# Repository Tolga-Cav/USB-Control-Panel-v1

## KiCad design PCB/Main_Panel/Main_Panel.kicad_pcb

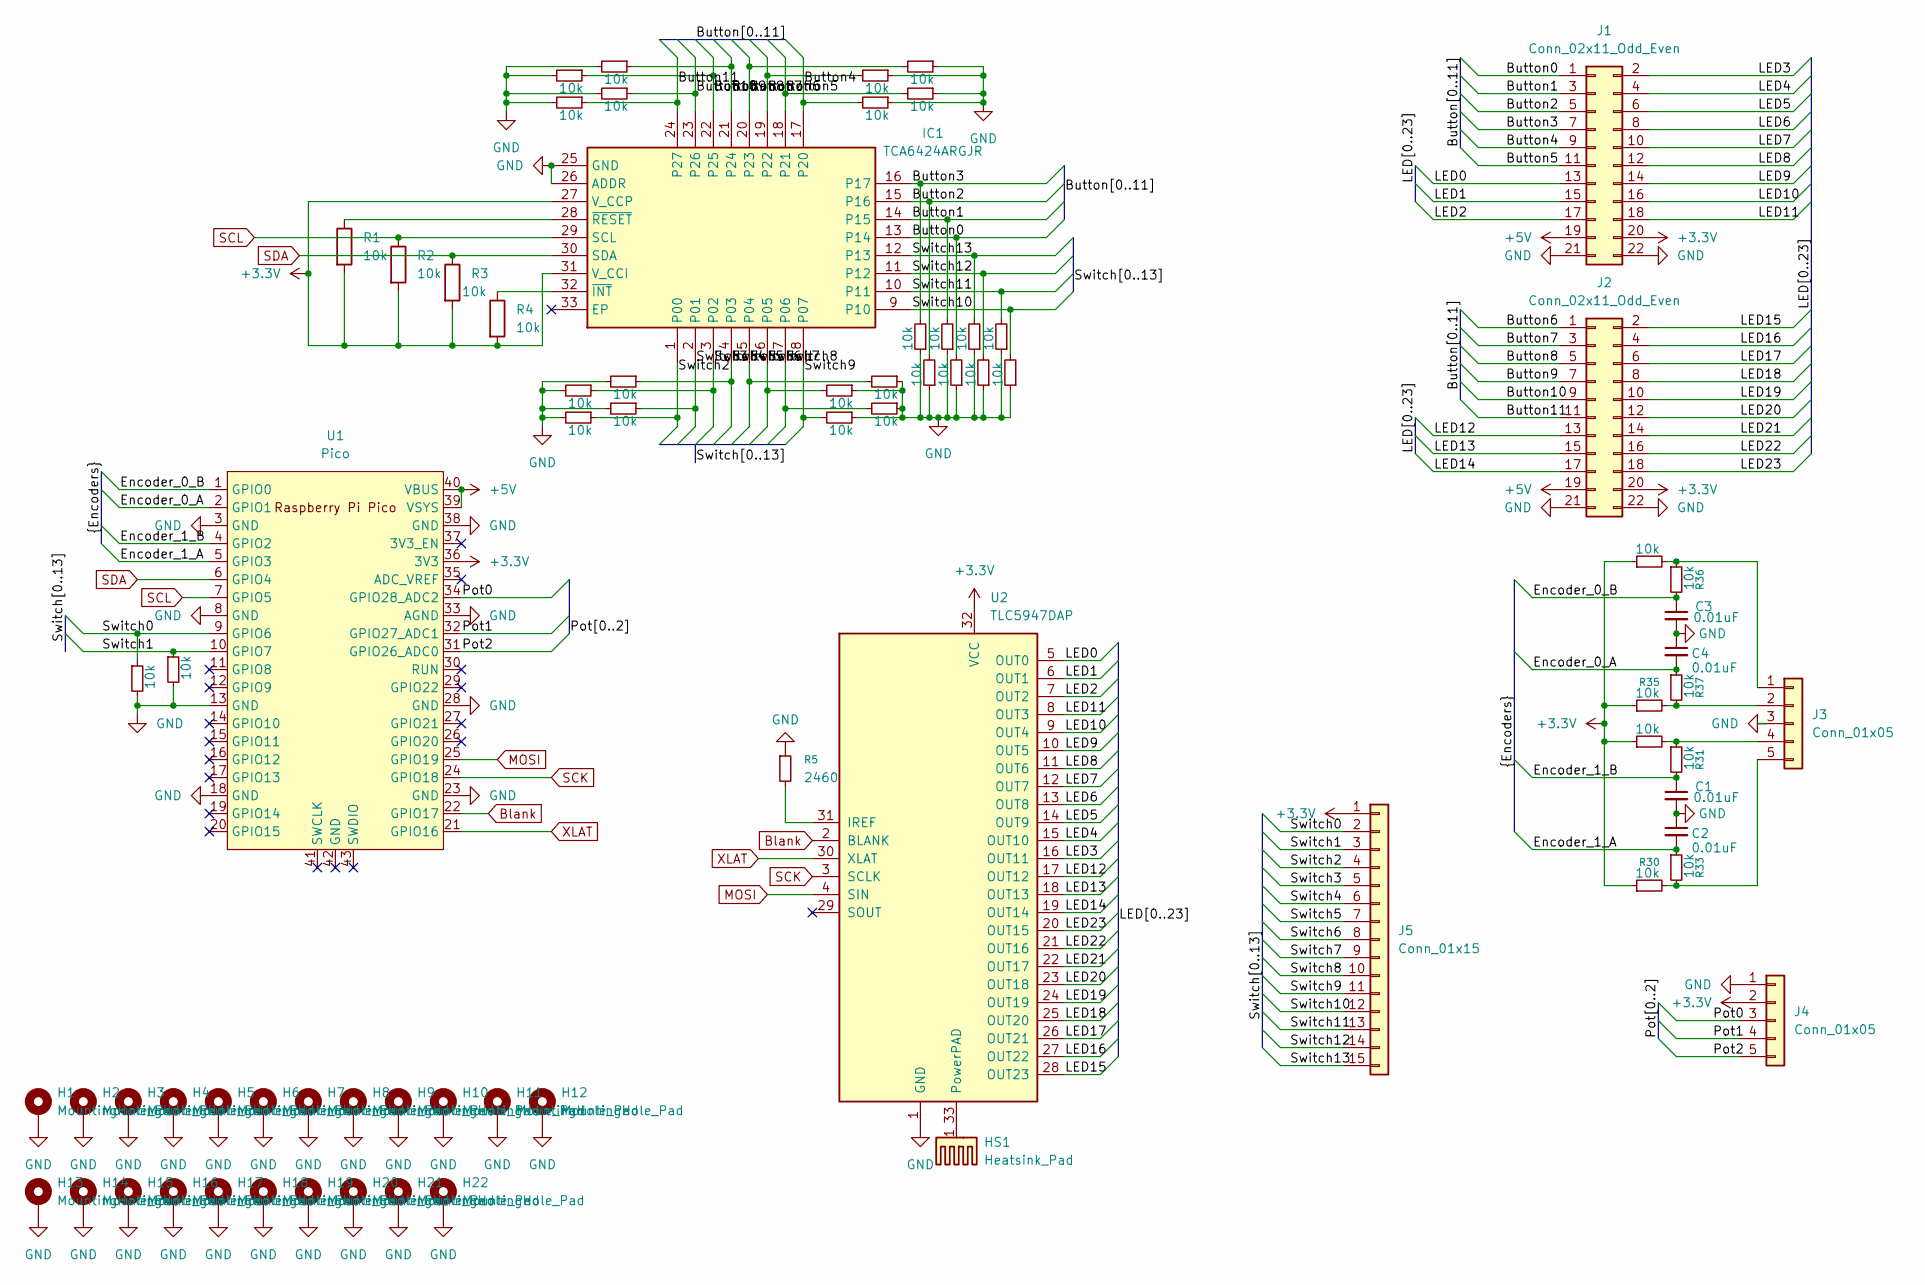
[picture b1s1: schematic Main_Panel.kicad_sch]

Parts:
C1, C2, C3, C4: 0.01uF; C_0805_2012Metric
H1, H2, H3, H4, H5, H6, H7, H8, H9, H10, H11, H12, H13, H14, H15, H16, H17, H18, H19, H20, H21, H22: MountingHole_Pad; MountingHole_3.2mm_M3_DIN965_Pad
HS1: Heatsink_Pad; Heat Sink
IC1: TCA6424ARGJR; QFN50P500X500X60-33N-D; Mouser Part Number 595-TCA6424ARGJR
J1, J2: Conn_02x11_Odd_Even; PinHeader_2x11_P2.54mm_Vertical
J3, J4: Conn_01x05; PinHeader_1x05_P2.54mm_Vertical
J5: Conn_01x15; PinHeader_1x15_P2.54mm_Vertical
R1, R2, R3, R4, R6, R7, R8, R9, R10, R11, R12, R13, R14, R15, R16, R17, R18, R19, R20, R21, R22, R23, R24, R25, R26, R27, R28, R29, R30, R31, R32, R33, R34, R35, R36, R37, R38, R39: 10k; R_0805_2012Metric
R5: 2460; R_0805_2012Metric
U1: Pico; RPi_Pico_SMD_TH
U2: TLC5947DAP; HTSSOP-32-1EP_6.1x11mm_P0.65mm_EP5.2x11mm_Mask4.11x4.36mm_T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

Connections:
+3.3V: IC1.27 (V_CCP), IC1.31 (V_CCI), J1.20, J2.20, J4.2, J5.1, R1.2, R2.2, R3.2, R4.2, R30.1, R32.1, R34.1, R35.1, U1.36 (3V3), U2.32 (VCC)
+5V: J1.19, J2.19, U1.39 (VSYS), U1.40 (VBUS)
/Button0: IC1.13 (P14), J1.1, R10.2
/Button1: IC1.14 (P15), J1.3, R7.2
/Button2: IC1.15 (P16), J1.5, R9.2
/Button3: IC1.16 (P17), J1.7, R6.2
/Button4: IC1.17 (P20), J1.9, R19.2
/Button5: IC1.18 (P21), J1.11, R21.2
/Button6: IC1.19 (P22), J2.1, R18.2
/Button7: IC1.20 (P23), J2.3, R20.2
/Button8: IC1.21 (P24), J2.5, R15.1
/Button9: IC1.22 (P25), J2.7, R14.1
/Button10: IC1.23 (P26), J2.9, R16.1
/Button11: IC1.24 (P27), J2.11, R17.1
/Encoder_0_A: C4.2, R37.1, U1.2 (GPIO1)
/Encoder_0_B: C3.1, R36.2, U1.1 (GPIO0)
/Encoder_1_A: C2.2, R33.1, U1.5 (GPIO3)
/Encoder_1_B: C1.1, R31.2, U1.4 (GPIO2)
/LED0: J1.13, U2.5 (OUT0)
/LED1: J1.15, U2.6 (OUT1)
/LED2: J1.17, U2.7 (OUT2)
/LED3: J1.2, U2.16 (OUT11)
/LED4: J1.4, U2.15 (OUT10)
/LED5: J1.6, U2.14 (OUT9)
/LED6: J1.8, U2.13 (OUT8)
/LED7: J1.10, U2.12 (OUT7)
/LED8: J1.12, U2.11 (OUT6)
/LED9: J1.14, U2.10 (OUT5)
/LED10: J1.16, U2.9 (OUT4)
/LED11: J1.18, U2.8 (OUT3)
/LED12: J2.13, U2.17 (OUT12)
/LED13: J2.15, U2.18 (OUT13)
/LED14: J2.17, U2.19 (OUT14)
/LED15: J2.2, U2.28 (OUT23)
/LED16: J2.4, U2.27 (OUT22)
/LED17: J2.6, U2.26 (OUT21)
/LED18: J2.8, U2.25 (OUT20)
/LED19: J2.10, U2.24 (OUT19)
/LED20: J2.12, U2.23 (OUT18)
/LED21: J2.14, U2.22 (OUT17)
/LED22: J2.16, U2.21 (OUT16)
/LED23: J2.18, U2.20 (OUT15)
/Pot0: J4.3, U1.34 (GPIO28_ADC2)
/Pot1: J4.4, U1.32 (GPIO27_ADC1)
/Pot2: J4.5, U1.31 (GPIO26_ADC0)
/Switch0: J5.2, R38.1, U1.9 (GPIO6)
/Switch1: J5.3, R39.1, U1.10 (GPIO7)
/Switch2: IC1.1 (P00), J5.4, R23.1
/Switch3: IC1.2 (P01), J5.5, R25.1
/Switch4: IC1.3 (P02), J5.6, R22.1
/Switch5: IC1.4 (P03), J5.7, R24.1
/Switch6: IC1.5 (P04), J5.8, R28.2
/Switch7: IC1.6 (P05), J5.9, R26.2
/Switch8: IC1.7 (P06), J5.10, R29.2
/Switch9: IC1.8 (P07), J5.11, R27.2
/Switch10: IC1.9 (P10), J5.12, R13.2
/Switch11: IC1.10 (P11), J5.13, R12.2
/Switch12: IC1.11 (P12), J5.14, R11.2
/Switch13: IC1.12 (P13), J5.15, R8.2
Blank: U1.22 (GPIO17), U2.2 (BLANK)
GND: C1.2, C2.1, C3.2, C4.1, H1.1, H2.1, H3.1, H4.1, H5.1, H6.1, H7.1, H8.1, H9.1, H10.1, H11.1, H12.1, H13.1, H14.1, H15.1, H16.1, H17.1, H18.1, H19.1, H20.1, H21.1, H22.1, IC1.25 (GND), IC1.26 (ADDR), J1.21, J1.22, J2.21, J2.22, J3.3, J4.1, R5.1, R6.1, R7.1, R8.1, R9.1, R10.1, R11.1, R12.1, R13.1, R14.2, R15.2, R16.2, R17.2, R18.1, R19.1, R20.1, R21.1, R22.2, R23.2, R24.2, R25.2, R26.1, R27.1, R28.1, R29.1, R38.2, R39.2, U1.3 (GND), U1.8 (GND), U1.13 (GND), U1.18 (GND), U1.23 (GND), U1.28 (GND), U1.33 (AGND), U1.38 (GND), U2.1 (GND)
MOSI: U1.25 (GPIO19), U2.4 (SIN)
unnamed: IC1.32 (~INT), R4.1
unnamed: IC1.28 (~RESET), R1.1
unnamed: J3.1, R34.2, R36.1
unnamed: J3.2, R35.2, R37.2
unnamed: J3.4, R31.1, R32.2
unnamed: J3.5, R30.2, R33.2
unnamed: R5.2, U2.31 (IREF)
unnamed: HS1.1, U2.33 (PowerPAD)
SCK: U1.24 (GPIO18), U2.3 (SCLK)
SCL: IC1.29 (SCL), R2.1, U1.7 (GPIO5)
SDA: IC1.30 (SDA), R3.1, U1.6 (GPIO4)
XLAT: U1.21 (GPIO16), U2.30 (XLAT)

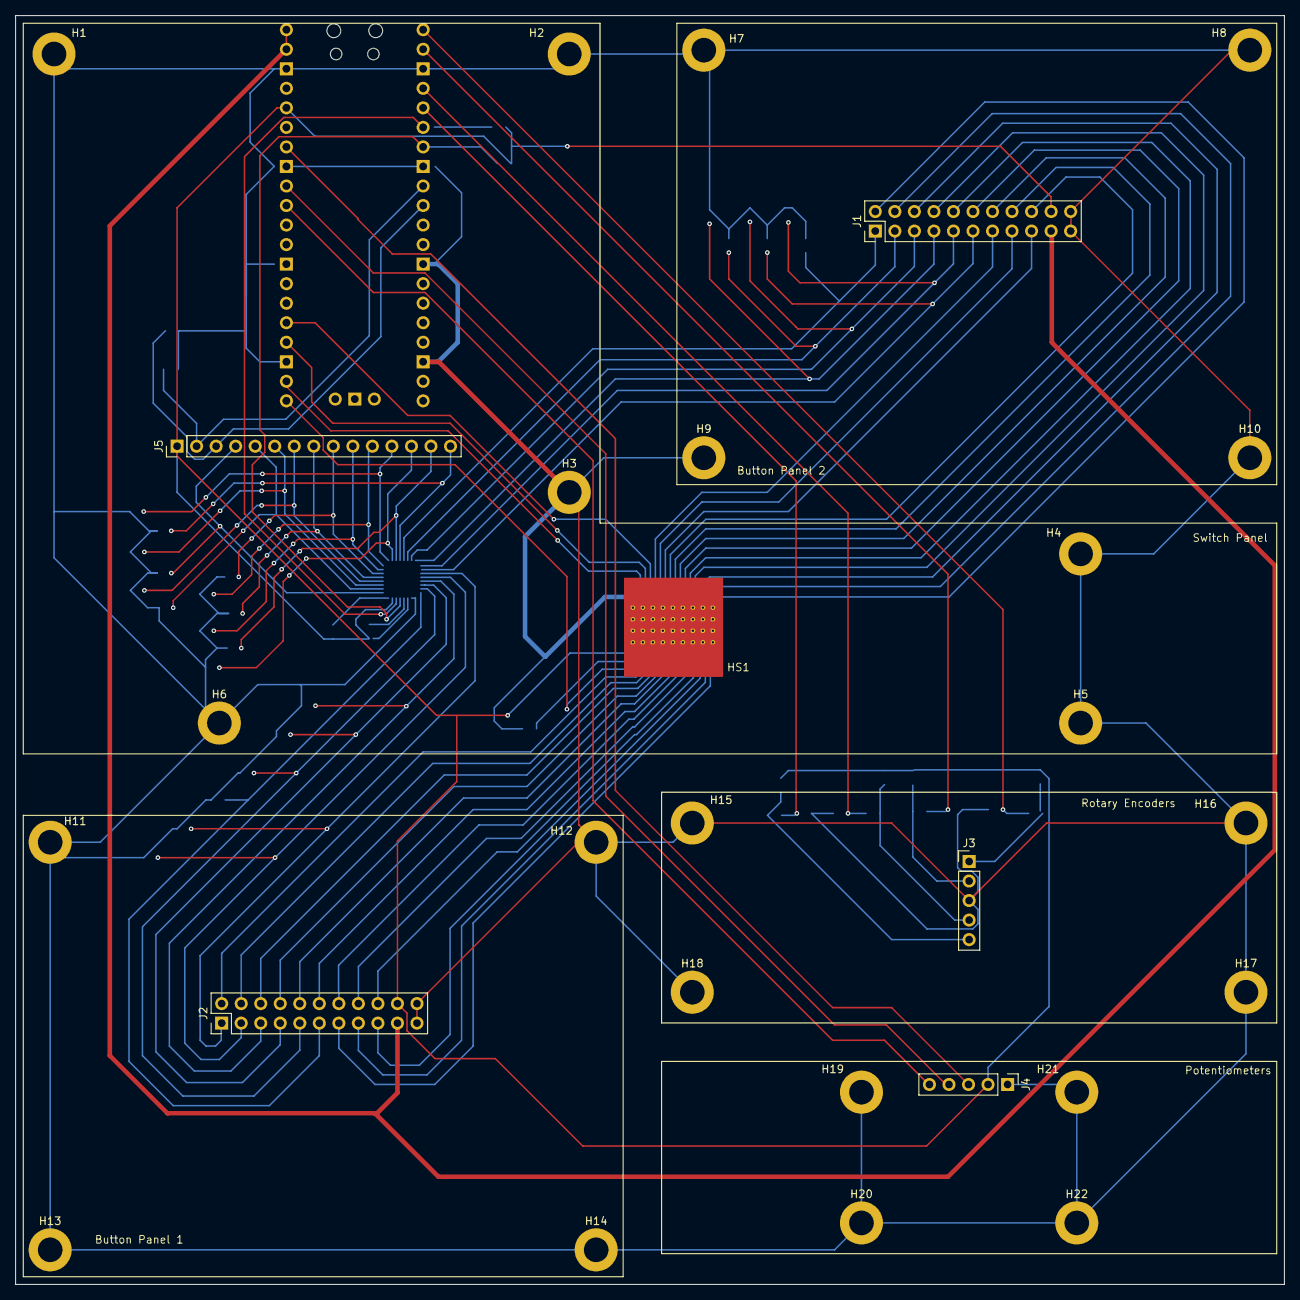
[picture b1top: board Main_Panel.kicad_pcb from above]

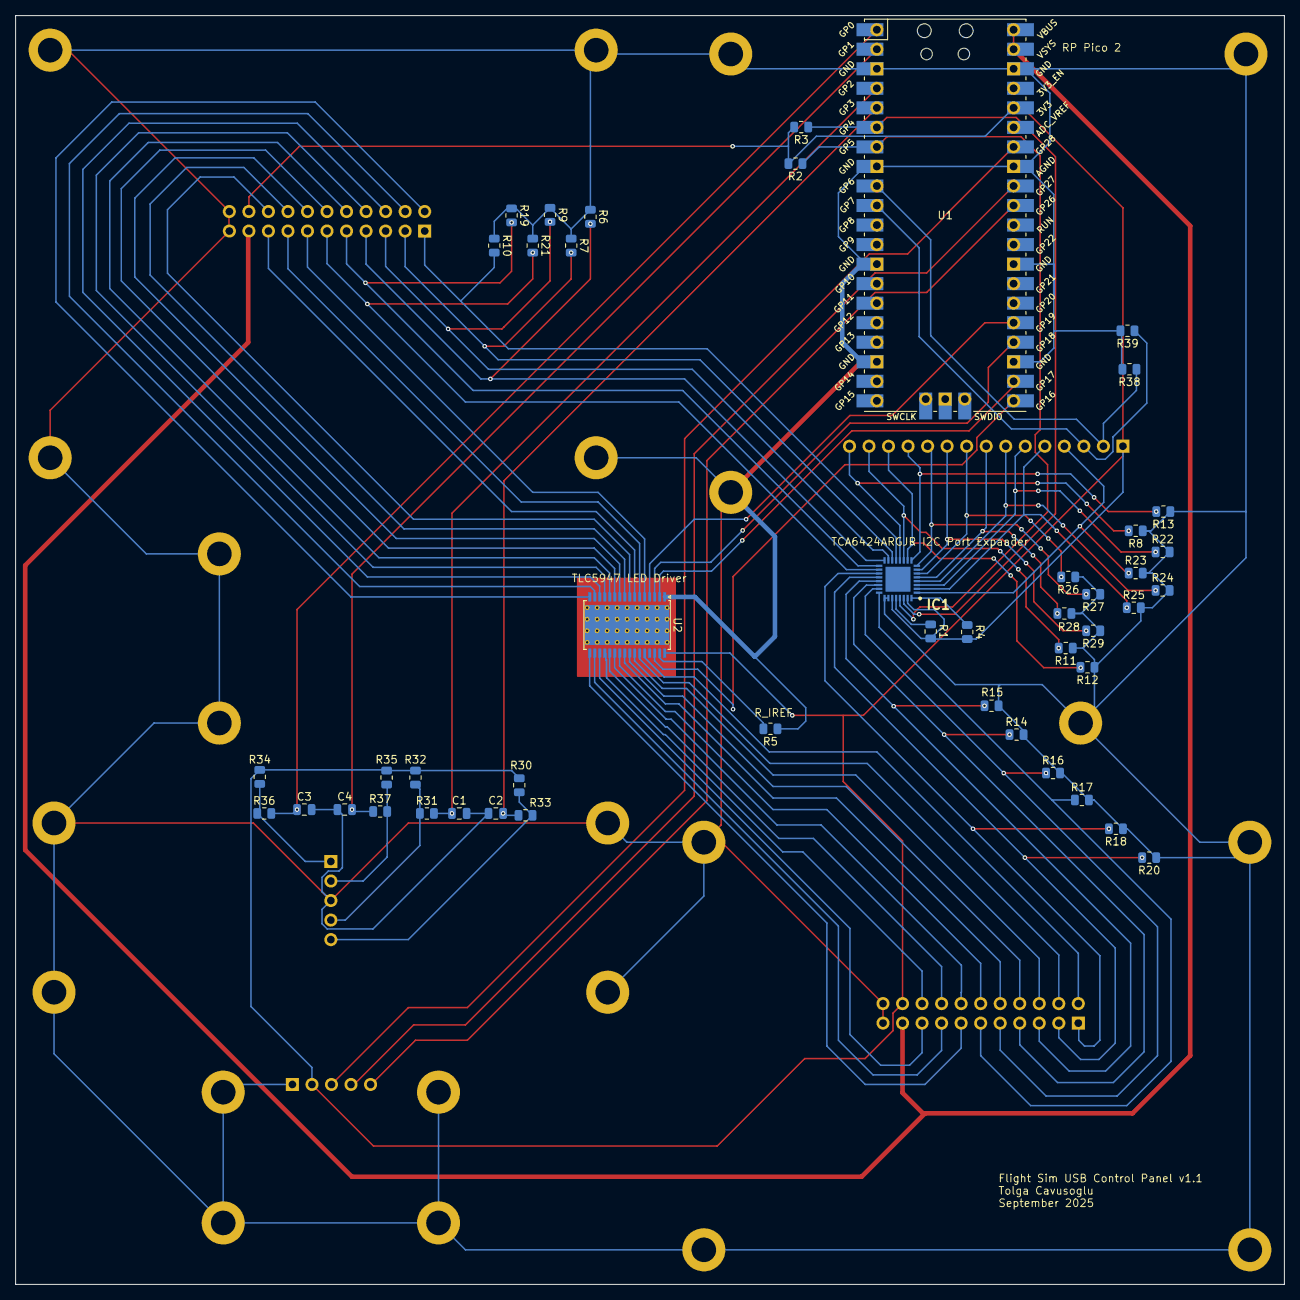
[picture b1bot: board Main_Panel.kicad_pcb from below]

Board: 2 copper layers, 165.0 x 165.0 mm, 74 parts (46 on the bottom side), 74 nets.

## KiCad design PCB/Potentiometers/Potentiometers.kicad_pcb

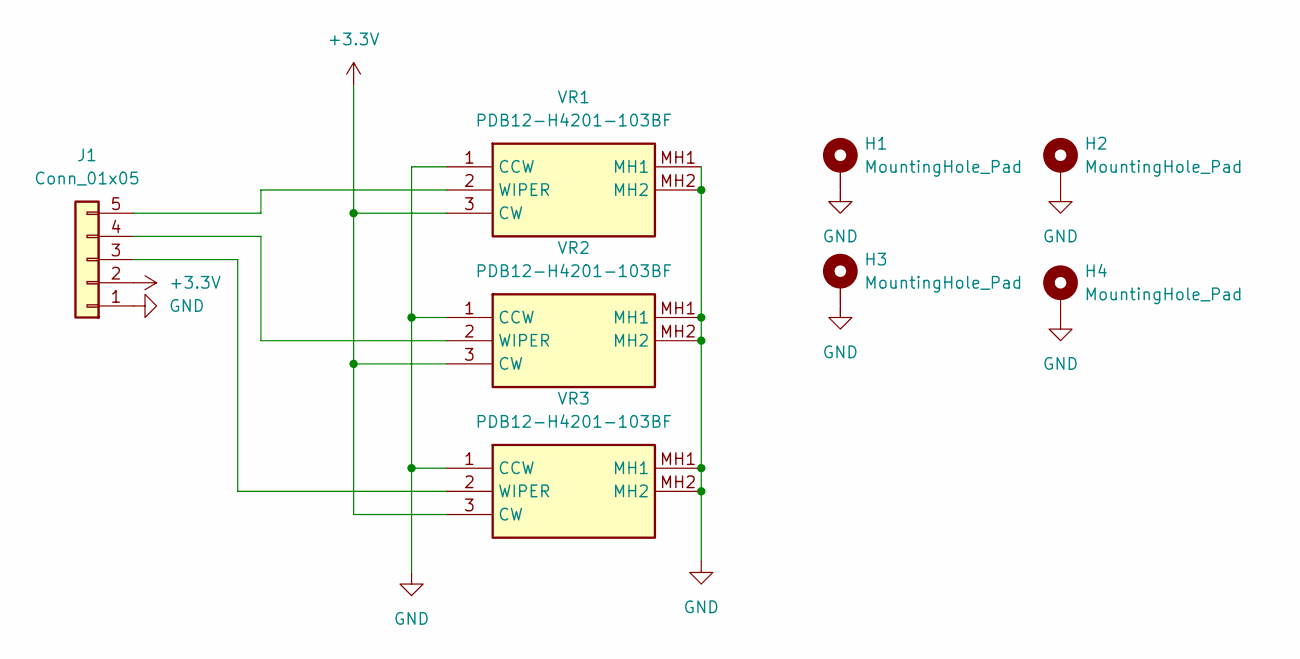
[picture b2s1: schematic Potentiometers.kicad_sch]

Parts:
H1, H2, H3, H4: MountingHole_Pad; MountingHole_3.2mm_M3_DIN965_Pad
J1: Conn_01x05; PinSocket_1x05_P2.54mm_Vertical
VR1, VR2, VR3: PDB12-H4201-103BF; PDB12H4201103BF; Mouser Part Number 652-PDB12-H4201103BF

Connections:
+3.3V: J1.2, VR1.3 (CW), VR2.3 (CW), VR3.3 (CW)
GND: H1.1, H2.1, H3.1, H4.1, J1.1, VR1.1 (CCW), VR1.MH1, VR1.MH2, VR2.1 (CCW), VR2.MH1, VR2.MH2, VR3.1 (CCW), VR3.MH1, VR3.MH2
unnamed: J1.3, VR3.2 (WIPER)
unnamed: J1.4, VR2.2 (WIPER)
unnamed: J1.5, VR1.2 (WIPER)

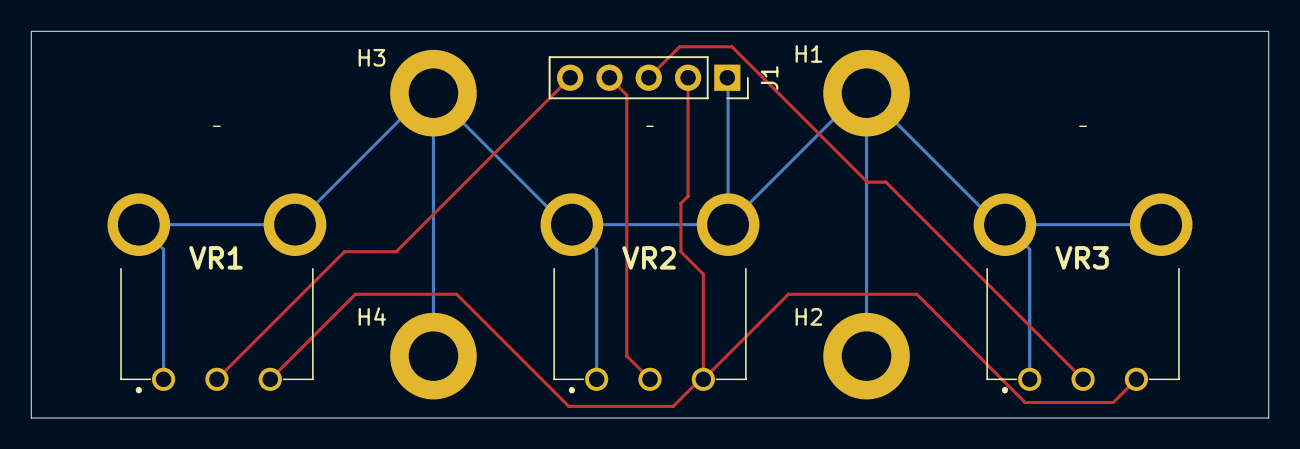
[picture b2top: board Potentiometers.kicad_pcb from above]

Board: 2 copper layers, 80.0 x 25.0 mm, 8 parts (0 on the bottom side), 5 nets.

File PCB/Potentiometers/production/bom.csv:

Designator,Footprint,Quantity,Value,LCSC Part #
J1,PinSocket_1x05_P2.54mm_Vertical,1,Conn_01x05,
"VR1, VR2, VR3",PDB12H4201103BF,3,PDB12-H4201-103BF,

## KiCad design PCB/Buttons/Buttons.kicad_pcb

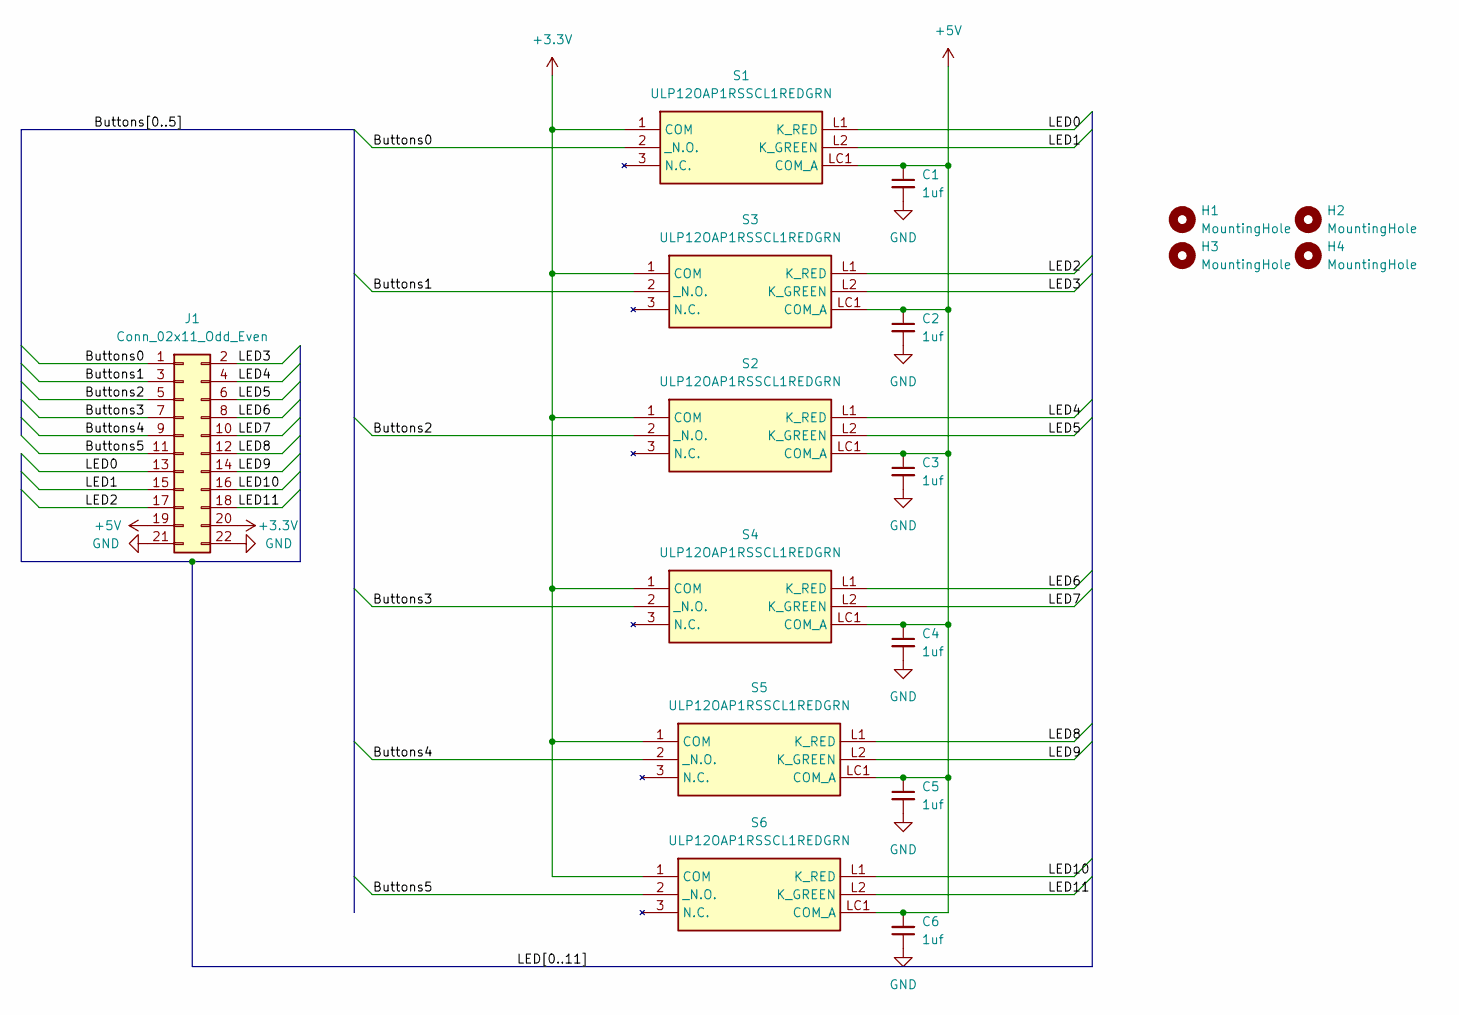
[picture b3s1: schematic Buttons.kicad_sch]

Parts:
C1, C2, C3, C4, C5, C6: 1uf; C_1206_3216Metric_Pad1.33x1.80mm_HandSolder
H1, H2, H3, H4: MountingHole; MountingHole_3.2mm_M3
J1: Conn_02x11_Odd_Even; PinHeader_2x11_P2.54mm_Vertical
S1, S2, S3, S4, S5, S6: ULP12OAP1RSSCL1REDGRN; Mouser Part Number 612-UP1RSSCL1REDGRN

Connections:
+3.3V: J1.20, S1.1 (COM), S2.1 (COM), S3.1 (COM), S4.1 (COM), S5.1 (COM), S6.1 (COM)
+5V: C1.1, C2.1, C3.1, C4.1, C5.1, C6.2, J1.19, S1.LC1 (COM_A), S2.LC1 (COM_A), S3.LC1 (COM_A), S4.LC1 (COM_A), S5.LC1 (COM_A), S6.LC1 (COM_A)
/Buttons0: J1.1, S1.2 (_N.O.)
/Buttons1: J1.3, S3.2 (_N.O.)
/Buttons2: J1.5, S2.2 (_N.O.)
/Buttons3: J1.7, S4.2 (_N.O.)
/Buttons4: J1.9, S5.2 (_N.O.)
/Buttons5: J1.11, S6.2 (_N.O.)
/LED0: J1.13, S1.L1 (K_RED)
/LED1: J1.15, S1.L2 (K_GREEN)
/LED2: J1.17, S3.L1 (K_RED)
/LED3: J1.2, S3.L2 (K_GREEN)
/LED4: J1.4, S2.L1 (K_RED)
/LED5: J1.6, S2.L2 (K_GREEN)
/LED6: J1.8, S4.L1 (K_RED)
/LED7: J1.10, S4.L2 (K_GREEN)
/LED8: J1.12, S5.L1 (K_RED)
/LED9: J1.14, S5.L2 (K_GREEN)
/LED10: J1.16, S6.L1 (K_RED)
/LED11: J1.18, S6.L2 (K_GREEN)
GND: C1.2, C2.2, C3.2, C4.2, C5.2, C6.1, J1.21, J1.22

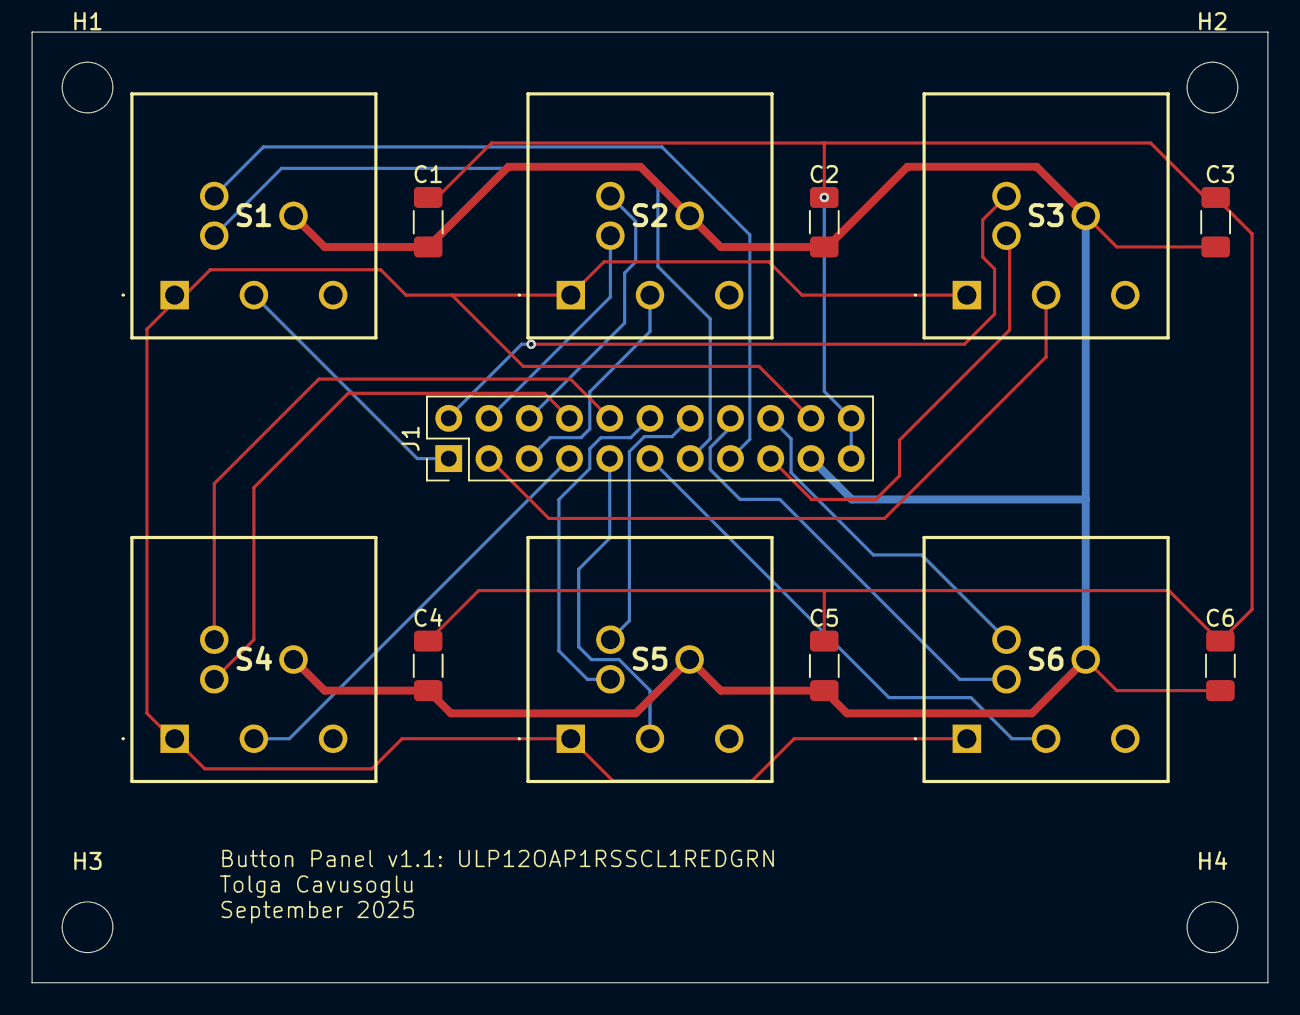
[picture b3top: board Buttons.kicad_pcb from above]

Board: 2 copper layers, 78.0 x 60.0 mm, 17 parts (0 on the bottom side), 21 nets.

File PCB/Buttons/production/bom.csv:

Designator,Footprint,Quantity,Value,LCSC Part #
"C1, C2, C3, C4, C5, C6",1206,6,1uf,
J1,PinSocket_2x11_P2.54mm_Vertical,1,Conn_02x11_Odd_Even,
"S1, S2, S3, S4, S5, S6",ULP12OAP1RSSCL1REDGRN,6,ULP12OAP1RSSCL1REDGRN,

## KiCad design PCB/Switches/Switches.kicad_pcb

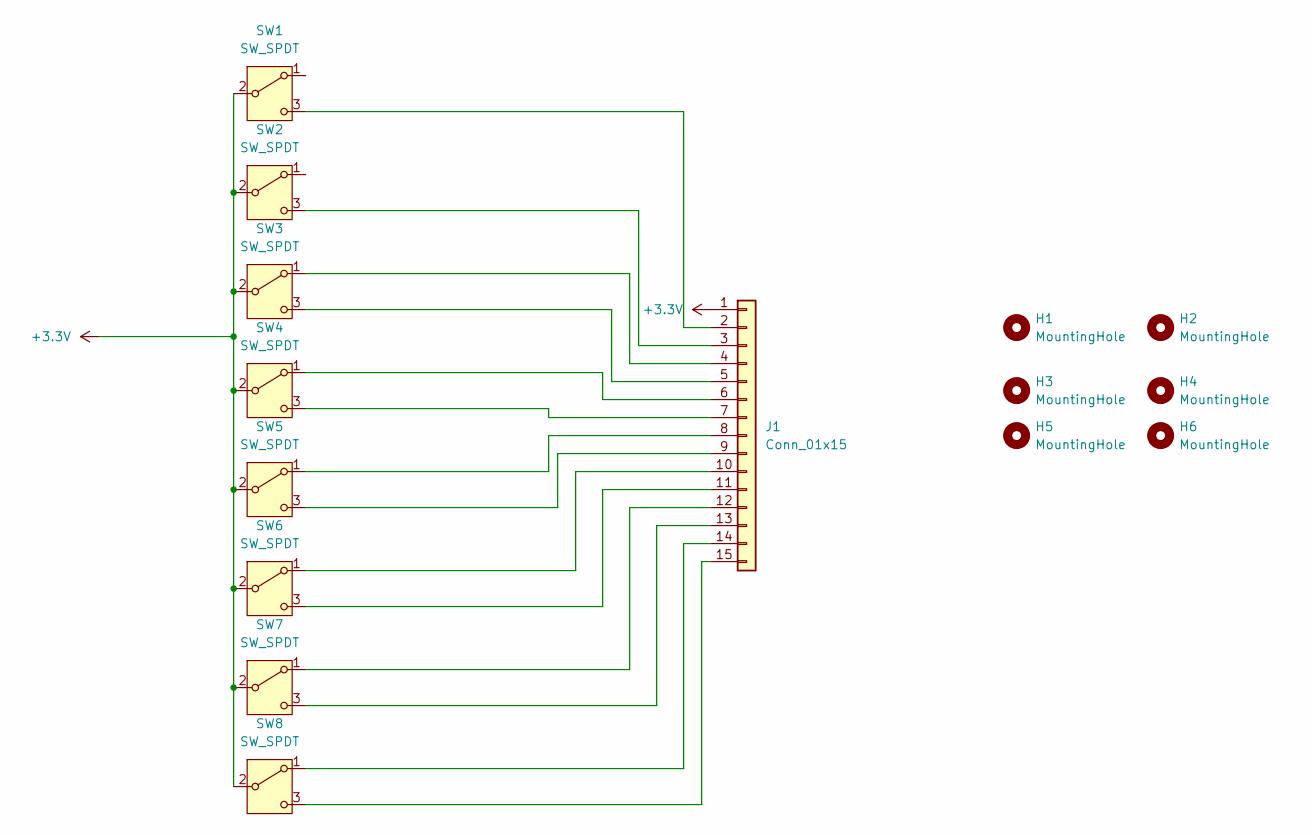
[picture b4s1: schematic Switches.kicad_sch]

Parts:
H1, H2, H3, H4, H5, H6: MountingHole; MountingHole_3.2mm_M3
J1: Conn_01x15; PinHeader_1x15_P2.54mm_Vertical
SW1, SW2, SW3, SW4, SW5, SW6, SW7, SW8: SW_SPDT; 100SP4T8B13VS2REH

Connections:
+3.3V: J1.1, SW1.2 (B), SW2.2 (B), SW3.2 (B), SW4.2 (B), SW5.2 (B), SW6.2 (B), SW7.2 (B), SW8.2 (B)
unnamed: J1.2, SW1.3 (C)
unnamed: J1.3, SW2.3 (C)
unnamed: J1.4, SW3.1 (A)
unnamed: J1.5, SW3.3 (C)
unnamed: J1.6, SW4.1 (A)
unnamed: J1.7, SW4.3 (C)
unnamed: J1.8, SW5.1 (A)
unnamed: J1.9, SW5.3 (C)
unnamed: J1.10, SW6.1 (A)
unnamed: J1.11, SW6.3 (C)
unnamed: J1.12, SW7.1 (A)
unnamed: J1.13, SW7.3 (C)
unnamed: J1.14, SW8.1 (A)
unnamed: J1.15, SW8.3 (C)

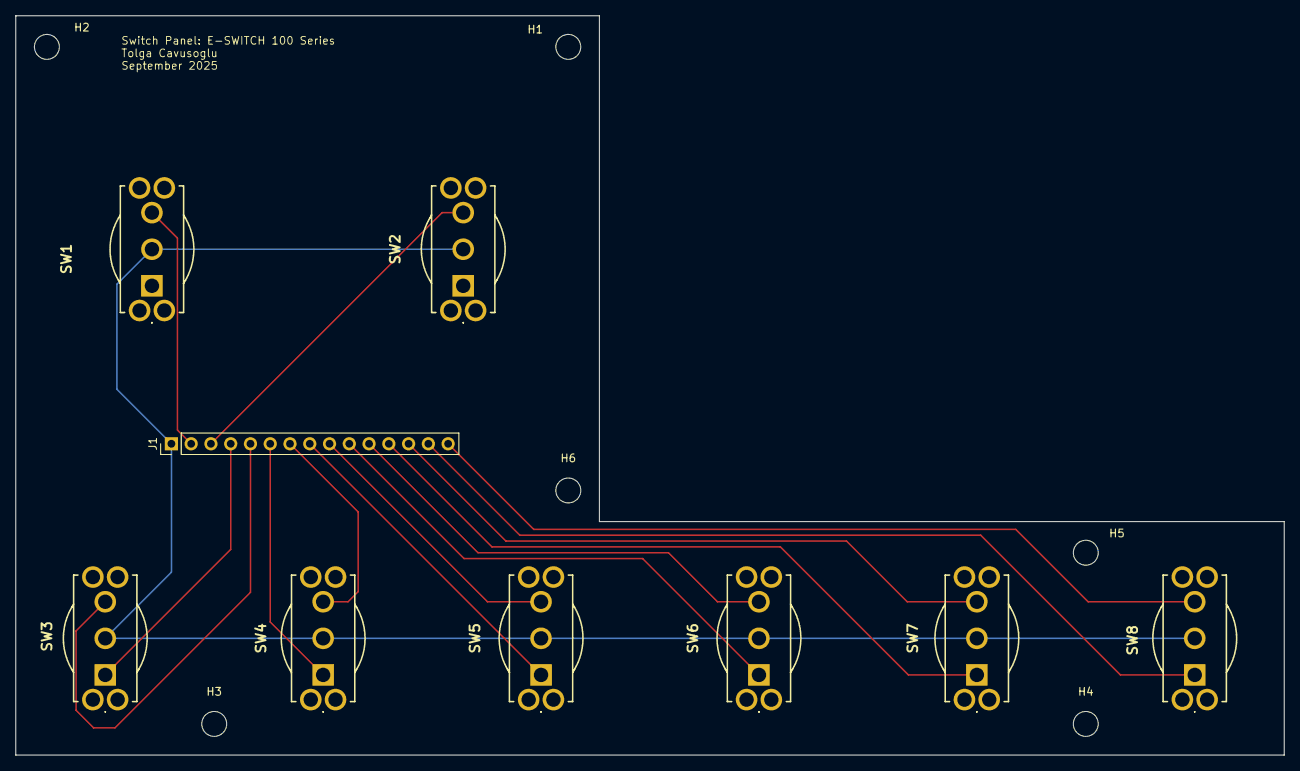
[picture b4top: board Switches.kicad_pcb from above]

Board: 2 copper layers, 163.0 x 95.0 mm, 15 parts (0 on the bottom side), 15 nets.

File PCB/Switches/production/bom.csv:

Designator,Footprint,Quantity,Value,LCSC Part #
J1,PinHeader_1x15_P2.54mm_Vertical,1,Conn_01x15,
"SW1, SW2, SW3, SW4, SW5, SW6, SW7, SW8",100SP4T8B13VS2REH,8,SW_SPDT,

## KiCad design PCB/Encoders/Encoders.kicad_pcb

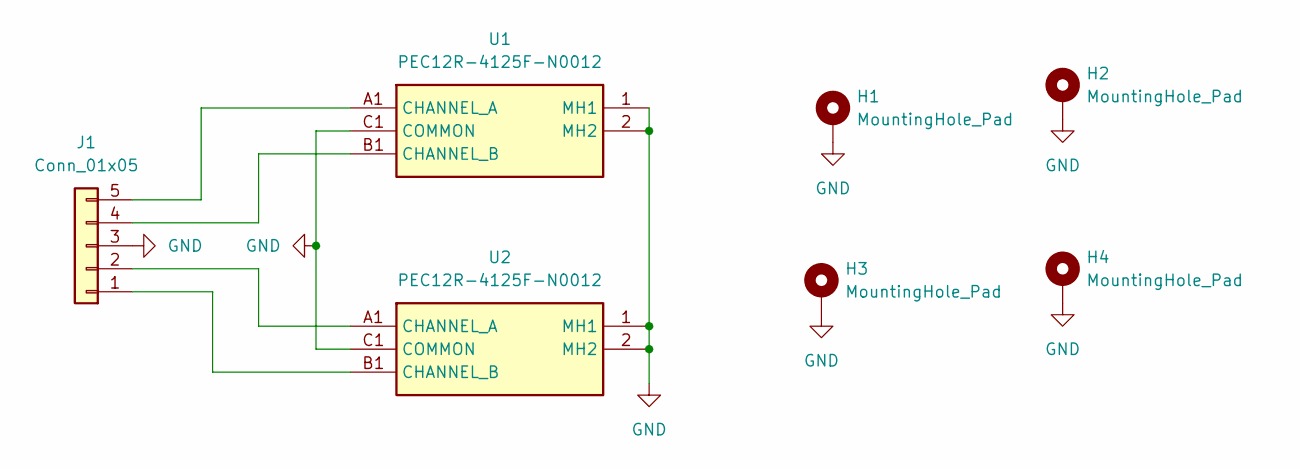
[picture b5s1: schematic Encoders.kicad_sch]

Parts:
H1, H2, H3, H4: MountingHole_Pad; MountingHole_3.2mm_M3_DIN965_Pad
J1: Conn_01x05; PinHeader_1x05_P2.54mm_Vertical
U1, U2: PEC12R-4125F-N0012; PEC12R4125FN0012; Mouser Part Number 652-PEC12R-4125F-N12

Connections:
GND: H1.1, H2.1, H3.1, H4.1, J1.3, U1.1 (MH1), U1.2 (MH2), U1.C1 (COMMON), U2.1 (MH1), U2.2 (MH2), U2.C1 (COMMON)
unnamed: J1.1, U2.B1 (CHANNEL_B)
unnamed: J1.2, U2.A1 (CHANNEL_A)
unnamed: J1.4, U1.B1 (CHANNEL_B)
unnamed: J1.5, U1.A1 (CHANNEL_A)

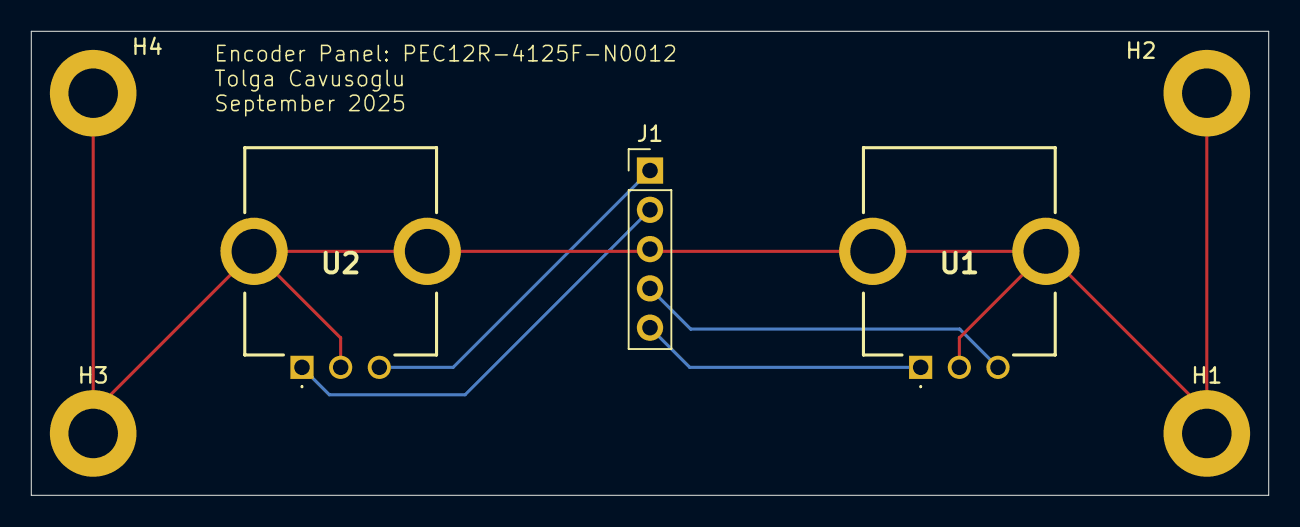
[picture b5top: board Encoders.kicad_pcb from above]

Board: 2 copper layers, 80.0 x 30.0 mm, 7 parts (0 on the bottom side), 5 nets.

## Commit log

2025-09-08 Added Cad files and created projects for all sub pcbs
2025-09-09 Fill kicad libraries
    Finished the kicad symbol and footprint libraries and linked them together so everything works as intended.
2025-09-15 Add Datasheets
2025-09-15 PCB Designs
2025-09-15 Begin CAD
2025-09-30 PCB Manufacturing Files and Full CAD
2025-10-12 Test code
2025-12-18 Update main and button pcbs to fix errors with v1.0
    Added pull downs to gpio expander and changed header footprint
2025-12-19 Update CAD
2025-12-19 Update potentiometer panel
    Increase the pitch between the pins of the potentiometers to account for disagreement between footprint found online and actual component
2025-12-21 Add manufacturing files for v1.1
